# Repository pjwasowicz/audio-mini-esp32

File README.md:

# Audio mini: a small stereo amplifier with Spotify, on an ESP32

*Polska wersja niżej: [przejdź do opisu po polsku](#audio-mini-mały-wzmacniacz-stereo-ze-spotify-na-esp32).*

*Audio mini with the lid off: the class-D amplifier module on the left, the 24 V power supply on the
right, the controller board with the ESP32 at the back, and the 14-segment display and volume knob on
the front panel.*

What I wanted was simple: pick up my phone, choose "Audio mini" in Spotify, and hear music from my
speakers. The TV and the turntable had to keep working too, all from one knob and one remote, with no
extra box that needs its own app.

So I built a small amplifier that does it. Inside the aluminium case there's a class-D amplifier module
(HW-576), a 24 V power supply and the controller board from this repository. The controller plays
Spotify, switches between Spotify, TV and the turntable with relays, and sets the volume with an analog
chip, so the TV and records never go through anything digital. The knob, the remote, the Spotify app
and a small web page all control the same volume. Turn the knob and the slider on your phone moves
with it.

It started on a Raspberry Pi. That worked, but a Pi is a whole computer to look after: an SD card, an
operating system, updates, and a slow start. The ESP32 version is ready a few seconds after you switch
it on, needs no looking after, and costs a fraction of the price.

## Using it

You pick "Audio mini" in the Spotify app like any other Connect speaker (you need Premium). Anyone at
home can connect from their own phone and account. After a power cut it remembers the last login and
connects again by itself.

Press play in Spotify and the amplifier switches to Spotify on its own. Switch to TV and Spotify pauses.

The knob, the remote, the phone and the web page all move the same volume. At low volume each click of
the knob is a small 1 dB step, so late-evening listening is easy to set. The shape of the volume curve
can be changed on the web page.

You shouldn't hear a pop when you switch it on or change inputs. The speakers have their own relay and
connect a couple of seconds later, once everything has power, the right input is on and the volume chip
has confirmed its settings twice.

On Spotify, after 30 seconds of silence the speakers disconnect and the display dims to a clock. TV and
the turntable switch off after 3 hours if nobody touches anything; press 2 or 3 on the remote to bring
them back.

The display is four red 14-segment characters, like on an 80s tuner. It shows the time, the scrolling
title and artist, "V 42" while you turn the volume, and the input name. On TV and the turntable a small
dot next to the clock tells you which one is on.

The remote is the cheap 21-button infrared kind: volume, play and pause, next and previous track,
inputs 1, 2 and 3, and mute.

The web page (`http://<device-address>:8080`) shows what's playing with the album cover, the volume,
the inputs, the volume curve and a few numbers about the device, like Wi-Fi signal and version.

To change the Wi-Fi network you don't need a computer: choose "CONF" in the knob menu, connect your
phone to the "Audio mini config" network, pick your home network and type the password.

New firmware goes over Wi-Fi with `make ota`, so the case stays closed.

## Setting it up

### The knob menu

Press the knob once and the display starts blinking the current input. Turn the knob to pick
`SPOT`, ` TV `, `PHON` or `CONF`, then press again to confirm. If you leave it alone for 8 seconds,
the menu closes without changing anything.

### Connecting to your Wi-Fi

You only need to do this once, or when you change your router or password.

1. Press the knob, turn to `CONF` and press again. The box restarts, and the display scrolls
   `WIFI: AUDIO MINI CONFIG 192.168.4.1`. Music stops while it's in this mode, but the inputs and the
   volume still work.
2. On your phone, open the Wi-Fi settings and join the network called **Audio mini config**. It has no
   password.
3. A setup page should open by itself, the same way hotel Wi-Fi login pages do. If it doesn't, open a
   browser and go to `192.168.4.1`.
4. Pick your home network from the list. For a hidden network, choose the last item,
   "Inna (ukryta) sieć…", and type its name in the box that appears.
5. Type your Wi-Fi password in the "Hasło" field and press "Zapisz i połącz". The page is in Polish,
   but those are the only two things to fill in.
6. The box restarts and joins your network. Your phone goes back to your home Wi-Fi on its own.

If nothing is saved within 5 minutes, the box gives up and starts normally with the old settings.

When the box can't reach your network, the display scrolls one of these instead of the clock:

| Message | What it means | What to do |
|---|---|---|
| `BAD WIFI PASSWORD` | the router turned the password down | run `CONF` again and retype it |
| `NO NETWORK` | it can't see a network with that name | check the name, or move the box closer to the router |
| `NO WIFI` | something else, often the router restarting | wait a minute; it keeps trying by itself |

### Connecting Spotify

1. Make sure your phone is on the same Wi-Fi as the box.
2. Open Spotify, start any song, tap the speaker icon at the bottom and choose **Audio mini**.
3. That's it. The box remembers the account and reconnects by itself after a power cut. Someone else at
   home can pick Audio mini from their own phone and account at any time.

### Finding the web page

The web page lives at `http://<device-address>:8080`. The easiest way to find the address is your
router's list of connected devices; the box shows up as `audio-mini`. On a Mac or iPhone,
`http://audio-mini.local:8080` usually works too.

### Settings for people building their own

The device name shown in Spotify, the network name, the pins and the `make ota` password are set at
build time in the "Audio mini (ESP32)" section of `idf.py menuconfig`. The defaults match the board in `pcb/`.

## The hardware

| Part | What it does | Connection |
|---|---|---|
| ESP32-DevKitC-VIE (ESP32-WROVER-IE, 8 MB PSRAM, external antenna) | brain, Wi-Fi, Spotify | (none) |
| PCM5102A DAC module | Spotify audio → analog | I2S: BCK 26, LCK 25, DIN 27 |
| PT2258 | analog volume control | I2C 0x44 (SDA 21, SCL 22) |
| HT16K33 + 4 × 14-segment LED (0.54") | display | I2C 0x70 |
| 3 relays | input selection Spotify / TV / Phono | GPIO 19 / 18 / 23 |
| relay | speakers on/off | ZAP1, GPIO 13 |
| VS1838 IR receiver + 21-button NEC remote | remote control | ZAP2, GPIO 5 |
| EC11 rotary encoder with button | volume and menu | A 32, B 33, button 14 |
| spare connector | for future ideas | ZAP3, GPIO 15 |

The KiCad files are in `pcb/`: `input_selector` is the main board (there's a PDF of the schematic too)
and `speaker_delay` is the small speaker relay board. The pictures below are 3D views from KiCad. The
ESP32, the DAC and the power module have no 3D models, so you only see their outlines.

| Main board (`input_selector`) | Speaker relay boards (`speaker_delay`) |
|---|---|
|  |  |

Along the top of the main board are the three input relays, the PT2258 volume chip and two regulators
that make 9 V for the volume chip and 12 V for the relays from the amplifier's 24 V. Along the bottom: the DAC module on the left, the ESP32 in the middle, and on the
right the spot for an LM2596 converter (U4), which I later swapped for a separate 5 V adapter.

### What I learned building it

The ESP32 needs its own 5 V power supply. When it shared power with the audio part, through either a
switching converter or a plain regulator, you could hear Wi-Fi in the speakers as a faint buzz. A
separate 5 V / 2 A adapter made it silent.

The DAC is much louder than the other inputs. The PCM5102A puts out about 2.1 V, several times more
than a TV or a turntable preamp, and Spotify came through far too loud even with the volume chip's
input turned well down. For now the firmware turns Spotify down 10 dB before the DAC and the volume chip
turns that input down another 78 dB. On the next board I'd put two resistors after the DAC to bring it
down to the level of the other inputs.

The relays disturb the wires to the volume chip. A command sent right after a relay clicked sometimes
arrived garbled, and the amplifier suddenly played very loud. Now the firmware sends all volume
settings again, twice, just before the speakers connect.

GPIO 5 is a bad pin for a relay. The ESP32 pulls it high while it starts, so anything on it switches on
before the program runs. The infrared receiver is happy there.

4 MB of flash is tight. With room for two copies of the firmware, needed for updates over Wi-Fi, about
100 KB is left. Next time I'd use the 8 or 16 MB version of the same module.

## Building and flashing

You need [ESP-IDF 5.5](https://docs.espressif.com/projects/esp-idf/) in `~/esp/esp-idf`. The Makefile
does the rest.

```bash
make            # first run asks for your Wi-Fi, downloads cspot and applies the patches
make flash      # flash over USB (PORT=/dev/cu.usbserial-XXXX if needed)
make ota        # flash over Wi-Fi (ADRES=192.168.1.130 by default)
make monitor    # serial log
make wifi       # change the Wi-Fi network stored at build time
```

Your Wi-Fi name and password stay in `sdkconfig.local`, which isn't in the repository. A network set
from the "CONF" menu wins over it. If you want `make ota` to ask for a password, set
`CONFIG_AUDIO_OTA_HASLO` in `menuconfig`; there's none by default.

The version number is `PROJECT_VER` in `CMakeLists.txt`. The display shows it for a few seconds after
switching on, and it's also in `/api/system`.

### Updating over Wi-Fi

Once the first version is on the board (over USB, with `make flash`), every later update can go over
Wi-Fi. The box can stay closed and connected to the amplifier.

```bash
make ota                          # builds and sends the new firmware to 192.168.1.130
make ota ADRES=192.168.1.57       # if your box has a different address
```

While it uploads, the display counts up (`U 12`, `U 45`, …). When it's done the box restarts by itself
and shows the new version number for a few seconds. Your settings stay as they were: Wi-Fi, the
Spotify login, volume and input. The whole thing takes about half a minute.

The flash holds two copies of the firmware. The new one is written next to the running one, and the box
only switches over once the upload is complete and checked, so a dropped connection halfway through
changes nothing. There's no automatic way back, though: if the new version doesn't start properly, you
need the USB cable again.

## Under the hood

The Spotify part isn't mine. It comes from [cspot](https://github.com/feelfreelinux/cspot), an
open-source Spotify client small enough to fit on a chip like the ESP32. The first `make` runs
`setup.sh`, which downloads it and applies my fixes from `patches/`.

Those fixes took most of the time. At first the box would play for a few minutes and then restart on its
own, usually right when I pressed pause or switched to TV. Once I tracked them down, the causes were:

- When you pause, the music fades out over half a second. The fade-out code went one step too far and
  wrote into memory that belonged to something else. That alone explains most of the restarts.
- The audio buffer had its "full" check backwards. When it filled up, bits of sound were cut off and
  the rest slid out of place.
- Every time the connection to Spotify dropped and came back, the part of the program that handles it
  ran out of working memory and crashed.
- The knob, the remote and the web page could all talk to Spotify at the same moment, and the library
  wasn't built for that.
- Right after start, a timer decided Spotify had been silent for ages and hung up.

On a weaker Wi-Fi signal the sound still stuttered. Two changes fixed it: a bigger buffer, now 9 seconds
of music, and switching off a sound-processing step that touched every sample even though it only does
anything during the pause fade-out. The chip was spending a lot of time on it, and decoding barely kept
up.

If you want to poke at it: the web page uses a small JSON API (`/api/status`, `/api/system`,
`/api/wejscie`, `/api/strojenie`, `/api/resety`). `/api/resety` lists the last ten restarts and why they
happened. Without it I would not have found the bugs above.

The full story of each bug, with the code and the fix, is in [docs/cspot-bledy.md](docs/cspot-bledy.md).

Code comments are in Polish.

## License

GPL-3.0 (see `LICENSE`), the same as cspot, which the Spotify part is built on.

---

# Audio mini: mały wzmacniacz stereo ze Spotify, na ESP32

*Audio mini bez pokrywy: moduł wzmacniacza klasy D z lewej, zasilacz 24 V z prawej, płytka sterownika
z ESP32 z tyłu, a na panelu przednim wyświetlacz 14-segmentowy i gałka głośności.*

Chciałem prostej rzeczy: biorę telefon, wybieram w Spotify „Audio mini” i słyszę muzykę z moich
kolumn. Telewizor i gramofon miały działać dalej, wszystko z jednej gałki i jednego pilota, bez
kolejnego pudełka z osobną aplikacją.

Zbudowałem więc mały wzmacniacz, który to robi. W aluminiowej obudowie jest moduł wzmacniacza klasy D
(HW-576), zasilacz 24 V i płytka sterownika z tego repozytorium. Sterownik gra Spotify, przełącza
przekaźnikami między Spotify, telewizorem i gramofonem, a głośność ustawia analogowym układem, więc
dźwięk z telewizora i z płyt nie przechodzi przez nic cyfrowego. Gałka, pilot, aplikacja Spotify i mała
strona WWW sterują tą samą głośnością. Kręcisz gałką, a suwak w telefonie przesuwa się razem z nią.

Zaczęło się od Raspberry Pi. Działało, ale Pi to cały komputer do pilnowania: karta SD, system,
aktualizacje i długi start. Wersja na ESP32 jest gotowa kilka sekund po włączeniu, nie trzeba się nią
opiekować i kosztuje ułamek ceny.

## Jak się z tego korzysta

„Audio mini” wybierasz w aplikacji Spotify jak każdy inny głośnik Connect (potrzebne jest Premium).
Każdy domownik może się połączyć ze swojego telefonu i konta. Po zaniku prądu urządzenie pamięta
ostatnie logowanie i łączy się samo.

Wciskasz „play” w Spotify i wzmacniacz sam przełącza się na Spotify. Przełączasz na telewizor
i Spotify się pauzuje.

Gałka, pilot, telefon i strona WWW przesuwają tę samą głośność. Przy cichym graniu każdy ząbek gałki to
mały krok o 1 dB, więc wieczorem łatwo trafić w odpowiedni poziom. Kształt krzywej głośności można
zmienić na stronie WWW.

Przy włączaniu i zmianie wejścia nie powinno nic stuknąć. Kolumny mają własny przekaźnik i dołączają
się kilka sekund później, gdy wszystko ma już zasilanie, włączone jest właściwe wejście, a układ
głośności dwa razy potwierdził ustawienia.

Na Spotify po 30 sekundach ciszy kolumny się odłączają, a wyświetlacz przygasa do zegara. Telewizor
i gramofon wyłączają się po 3 godzinach, jeśli nikt niczego nie dotyka; przycisk 2 albo 3 na pilocie
włącza je z powrotem.

Wyświetlacz to cztery czerwone znaki 14-segmentowe, jak w tunerze z lat 80. Pokazuje godzinę,
przewijany tytuł i wykonawcę, „V 42” przy kręceniu głośnością i nazwę wejścia. Na telewizorze
i gramofonie mała kropka przy zegarze mówi, które z nich gra.

Pilot to ten tani, na podczerwień, z 21 przyciskami: głośność, pauza, następny i poprzedni utwór,
wejścia 1, 2 i 3 oraz wyciszenie.

Strona WWW (`http://<adres-urządzenia>:8080`) pokazuje, co gra, razem z okładką, a do tego głośność,
wejścia, krzywą głośności i kilka liczb o urządzeniu, na przykład siłę Wi-Fi i wersję.

Do zmiany sieci Wi-Fi nie potrzeba komputera: w menu gałki wybierasz „CONF”, łączysz telefon z siecią
„Audio mini config”, wybierasz swoją sieć i wpisujesz hasło.

Nowy program idzie przez Wi-Fi poleceniem `make ota`, więc obudowa zostaje zamknięta.

## Pierwsze uruchomienie

### Menu gałki

Wciśnij gałkę raz, a wyświetlacz zacznie migać nazwą obecnego wejścia. Kręć, żeby wybrać `SPOT`,
` TV `, `PHON` albo `CONF`, i wciśnij jeszcze raz, żeby zatwierdzić. Jeśli przez 8 sekund nic nie
ruszysz, menu zamknie się bez zmian.

### Połączenie z Twoim Wi-Fi

Robisz to raz, albo po zmianie routera lub hasła.

1. Wciśnij gałkę, przekręć do `CONF` i wciśnij jeszcze raz. Urządzenie uruchomi się ponownie,
   a wyświetlacz zacznie przewijać `WIFI: AUDIO MINI CONFIG 192.168.4.1`. W tym trybie Spotify nie gra,
   ale wejścia i głośność działają.
2. W telefonie otwórz ustawienia Wi-Fi i połącz się z siecią **Audio mini config**. Nie ma hasła.
3. Strona konfiguracji powinna otworzyć się sama, tak jak strony logowania do Wi-Fi w hotelu. Jeśli się
   nie otworzy, wpisz w przeglądarce `192.168.4.1`.
4. Wybierz swoją sieć z listy. Dla sieci ukrytej wybierz ostatnią pozycję, „Inna (ukryta) sieć…”,
   i wpisz jej nazwę w polu, które się pojawi.
5. Wpisz hasło do Wi-Fi w polu „Hasło” i naciśnij „Zapisz i połącz”.
6. Urządzenie uruchomi się ponownie i połączy z Twoją siecią. Telefon sam wróci do domowego Wi-Fi.

Jeśli przez 5 minut nic nie zapiszesz, urządzenie odpuści i wystartuje normalnie, ze starymi
ustawieniami.

Gdy urządzenie nie może połączyć się z siecią, zamiast zegara przewija jeden z napisów:

| Napis | Co znaczy | Co zrobić |
|---|---|---|
| `BAD WIFI PASSWORD` | router odrzucił hasło | wejdź jeszcze raz w `CONF` i wpisz je ponownie |
| `NO NETWORK` | nie widzi sieci o tej nazwie | sprawdź nazwę albo przestaw urządzenie bliżej routera |
| `NO WIFI` | coś innego, często restart routera | poczekaj chwilę, łączy się samo |

### Połączenie ze Spotify

1. Sprawdź, czy telefon jest w tej samej sieci Wi-Fi co urządzenie.
2. Otwórz Spotify, puść dowolny utwór, dotknij ikony głośnika na dole i wybierz **Audio mini**.
3. To wszystko. Urządzenie zapamięta konto i po zaniku prądu połączy się samo. Inny domownik może
   w każdej chwili wybrać Audio mini ze swojego telefonu i konta.

### Gdzie jest strona WWW

Strona jest pod adresem `http://<adres-urządzenia>:8080`. Najłatwiej znaleźć adres na liście
podłączonych urządzeń w routerze; urządzenie widać tam jako `audio-mini`. Na Macu i iPhonie zwykle
działa też `http://audio-mini.local:8080`.

### Ustawienia dla budujących

Nazwę widoczną w Spotify, nazwę w sieci, piny i hasło do `make ota` ustawia się przed kompilacją
w części „Audio mini (ESP32)” w `idf.py menuconfig`. Domyślne wartości pasują do płytki z `pcb/`.

## Sprzęt

| Element | Do czego | Połączenie |
|---|---|---|
| ESP32-DevKitC-VIE (ESP32-WROVER-IE, 8 MB PSRAM, antena zewnętrzna) | mózg, Wi-Fi, Spotify | (brak) |
| moduł DAC PCM5102A | dźwięk Spotify → analog | I2S: BCK 26, LCK 25, DIN 27 |
| PT2258 | analogowa regulacja głośności | I2C 0x44 (SDA 21, SCL 22) |
| HT16K33 + 4 × LED 14-seg (0,54") | wyświetlacz | I2C 0x70 |
| 3 przekaźniki | wybór wejścia Spotify / TV / Phono | GPIO 19 / 18 / 23 |
| przekaźnik | dołączanie kolumn | ZAP1, GPIO 13 |
| odbiornik IR VS1838 + pilot NEC 21 przycisków | pilot | ZAP2, GPIO 5 |
| enkoder EC11 z przyciskiem | głośność i menu | A 32, B 33, przycisk 14 |
| wolne złącze | na przyszłe pomysły | ZAP3, GPIO 15 |

Pliki KiCad są w `pcb/`: `input_selector` to płyta główna (schemat jest też w PDF), a `speaker_delay`
to mała płytka przekaźnika kolumn. Obrazki niżej to widoki 3D z KiCad. ESP32, DAC i moduł zasilania nie
mają modeli 3D, więc widać tylko ich obrysy.

| Płyta główna (`input_selector`) | Płytki przekaźnika kolumn (`speaker_delay`) |
|---|---|
|  |  |

U góry płyty głównej są trzy przekaźniki wejść, układ głośności PT2258 i dwa stabilizatory, które
z 24 V wzmacniacza robią 9 V dla układu głośności i 12 V dla przekaźników.
Na dole: moduł DAC z lewej, ESP32 w środku, a z prawej miejsce na przetwornicę LM2596 (U4), którą
później zamieniłem na osobny zasilacz 5 V.

### Czego się nauczyłem przy budowie

ESP32 potrzebuje osobnego zasilacza 5 V. Gdy dzielił zasilanie z częścią audio, czy to przez
przetwornicę, czy przez zwykły stabilizator, Wi-Fi było słychać w kolumnach jako ciche brzęczenie.
Osobny zasilacz 5 V / 2 A dał ciszę.

DAC jest dużo głośniejszy od pozostałych wejść. PCM5102A daje około 2,1 V, kilka razy więcej niż
telewizor czy przedwzmacniacz gramofonowy, i Spotify grało o wiele za głośno, nawet przy mocno
ściszonym wejściu w układzie głośności. Na razie program ścisza Spotify o 10 dB przed DAC, a układ
głośności to wejście jeszcze o 78 dB. W następnej płytce dałbym dwa rezystory za DAC, żeby sprowadzić
go do poziomu pozostałych wejść.

Przekaźniki zakłócają przewody do układu głośności. Polecenie wysłane tuż po kliknięciu przekaźnika
dochodziło czasem przekłamane i wzmacniacz nagle grał bardzo głośno. Teraz program wysyła wszystkie
ustawienia głośności jeszcze raz, dwa razy, tuż przed dołączeniem kolumn.

GPIO 5 to zły pin na przekaźnik. ESP32 przy starcie ustawia na nim stan wysoki, więc to, co jest do
niego podłączone, włącza się, zanim ruszy program. Odbiornikowi podczerwieni to nie przeszkadza.

4 MB pamięci flash to mało. Przy miejscu na dwie kopie programu, potrzebnym do aktualizacji przez
Wi-Fi, zostaje około 100 KB. Następnym razem wziąłbym ten sam moduł w wersji z 8 albo 16 MB.

## Kompilacja i wgrywanie

Potrzebny jest [ESP-IDF 5.5](https://docs.espressif.com/projects/esp-idf/) w `~/esp/esp-idf`. Resztą
zajmuje się Makefile.

```bash
make            # za pierwszym razem pyta o Wi-Fi, pobiera cspot i nakłada łatki
make flash      # wgranie przez USB (PORT=/dev/cu.usbserial-XXXX, jeśli trzeba)
make ota        # wgranie przez Wi-Fi (domyślnie ADRES=192.168.1.130)
make monitor    # komunikaty z ESP32
make wifi       # zmiana sieci Wi-Fi zapisanej przy kompilacji
```

Nazwa Twojej sieci i hasło zostają w `sdkconfig.local`, którego nie ma w repozytorium. Sieć ustawiona
z menu „CONF” ma przed nią pierwszeństwo. Jeśli chcesz, żeby `make ota` pytało o hasło, ustaw
`CONFIG_AUDIO_OTA_HASLO` w `menuconfig`; domyślnie hasła nie ma.

Numer wersji to `PROJECT_VER` w `CMakeLists.txt`. Wyświetlacz pokazuje go przez kilka sekund po
włączeniu, jest też w `/api/system`.

### Aktualizacja przez Wi-Fi

Gdy pierwsza wersja jest już na płytce (przez USB, `make flash`), każdą następną można wgrać przez
Wi-Fi. Obudowa zostaje zamknięta, a urządzenie podłączone do wzmacniacza.

```bash
make ota                          # kompiluje i wysyła nowy program do 192.168.1.130
make ota ADRES=192.168.1.57       # jeśli Twoje urządzenie ma inny adres
```

W trakcie wysyłania wyświetlacz odlicza (`U 12`, `U 45`, …). Po wszystkim urządzenie samo się
restartuje i przez kilka sekund pokazuje nowy numer wersji. Ustawienia zostają bez zmian: Wi-Fi, login
Spotify, głośność i wejście. Całość trwa około pół minuty.

Pamięć mieści dwie kopie programu. Nowa zapisuje się obok działającej, a urządzenie przełącza się na nią
dopiero wtedy, gdy przyszła w całości i jest sprawdzona, więc przerwane połączenie w połowie niczego nie
psuje. Nie ma za to automatycznego powrotu: jeśli nowa wersja nie wystartuje poprawnie, potrzebny jest
znowu kabel USB.

## Pod spodem

Część od Spotify nie jest moja. To [cspot](https://github.com/feelfreelinux/cspot), otwarty klient
Spotify na tyle mały, że mieści się w ESP32. Przy pierwszym `make` skrypt `setup.sh` pobiera go
i nakłada moje poprawki z `patches/`.

Na te poprawki poszło najwięcej czasu. Na początku urządzenie grało kilka minut i samo się restartowało,
najczęściej wtedy, gdy wciskałem pauzę albo przełączałem na telewizor. Przyczyny okazały się takie:

- Przy pauzie muzyka cichnie przez pół sekundy. Kod tego wyciszania robił o jeden krok za dużo
  i zapisywał w pamięci, która należała do czegoś innego. To tłumaczy większość restartów.
- Bufor dźwięku miał odwrotnie sprawdzane, czy jest pełny. Gdy się zapełnił, kawałki muzyki były
  ucinane, a reszta się rozjeżdżała.
- Za każdym razem, gdy połączenie ze Spotify zrywało się i wracało, części programu, która się tym
  zajmuje, brakowało pamięci roboczej i padała.
- Gałka, pilot i strona WWW mogły odezwać się do Spotify w tej samej chwili, a biblioteka nie była na
  to przygotowana.
- Zaraz po starcie licznik uznawał, że Spotify od dawna milczy, i rozłączał.

Przy słabszym Wi-Fi dźwięk dalej się zacinał. Pomogły dwie zmiany: większy bufor, teraz na 9 sekund
muzyki, i wyłączenie przetwarzania dźwięku, które obrabiało każdą próbkę, choć do czegokolwiek jest
potrzebne tylko przy wyciszaniu na pauzę. Procesor tracił na nie sporo czasu i dekodowanie ledwo
nadążało.

Jeśli chcesz pogrzebać: strona WWW korzysta z małego API w JSON (`/api/status`, `/api/system`,
`/api/wejscie`, `/api/strojenie`, `/api/resety`). `/api/resety` pokazuje dziesięć ostatnich restartów
z przyczyną. Bez niego tych błędów bym nie znalazł.

Dokładny opis każdego błędu, z kodem i poprawką, jest w [docs/cspot-bledy.md](docs/cspot-bledy.md).

Komentarze w kodzie są po polsku.

## Licencja

GPL-3.0 (plik `LICENSE`), tak samo jak cspot, na którym opiera się część od Spotify.

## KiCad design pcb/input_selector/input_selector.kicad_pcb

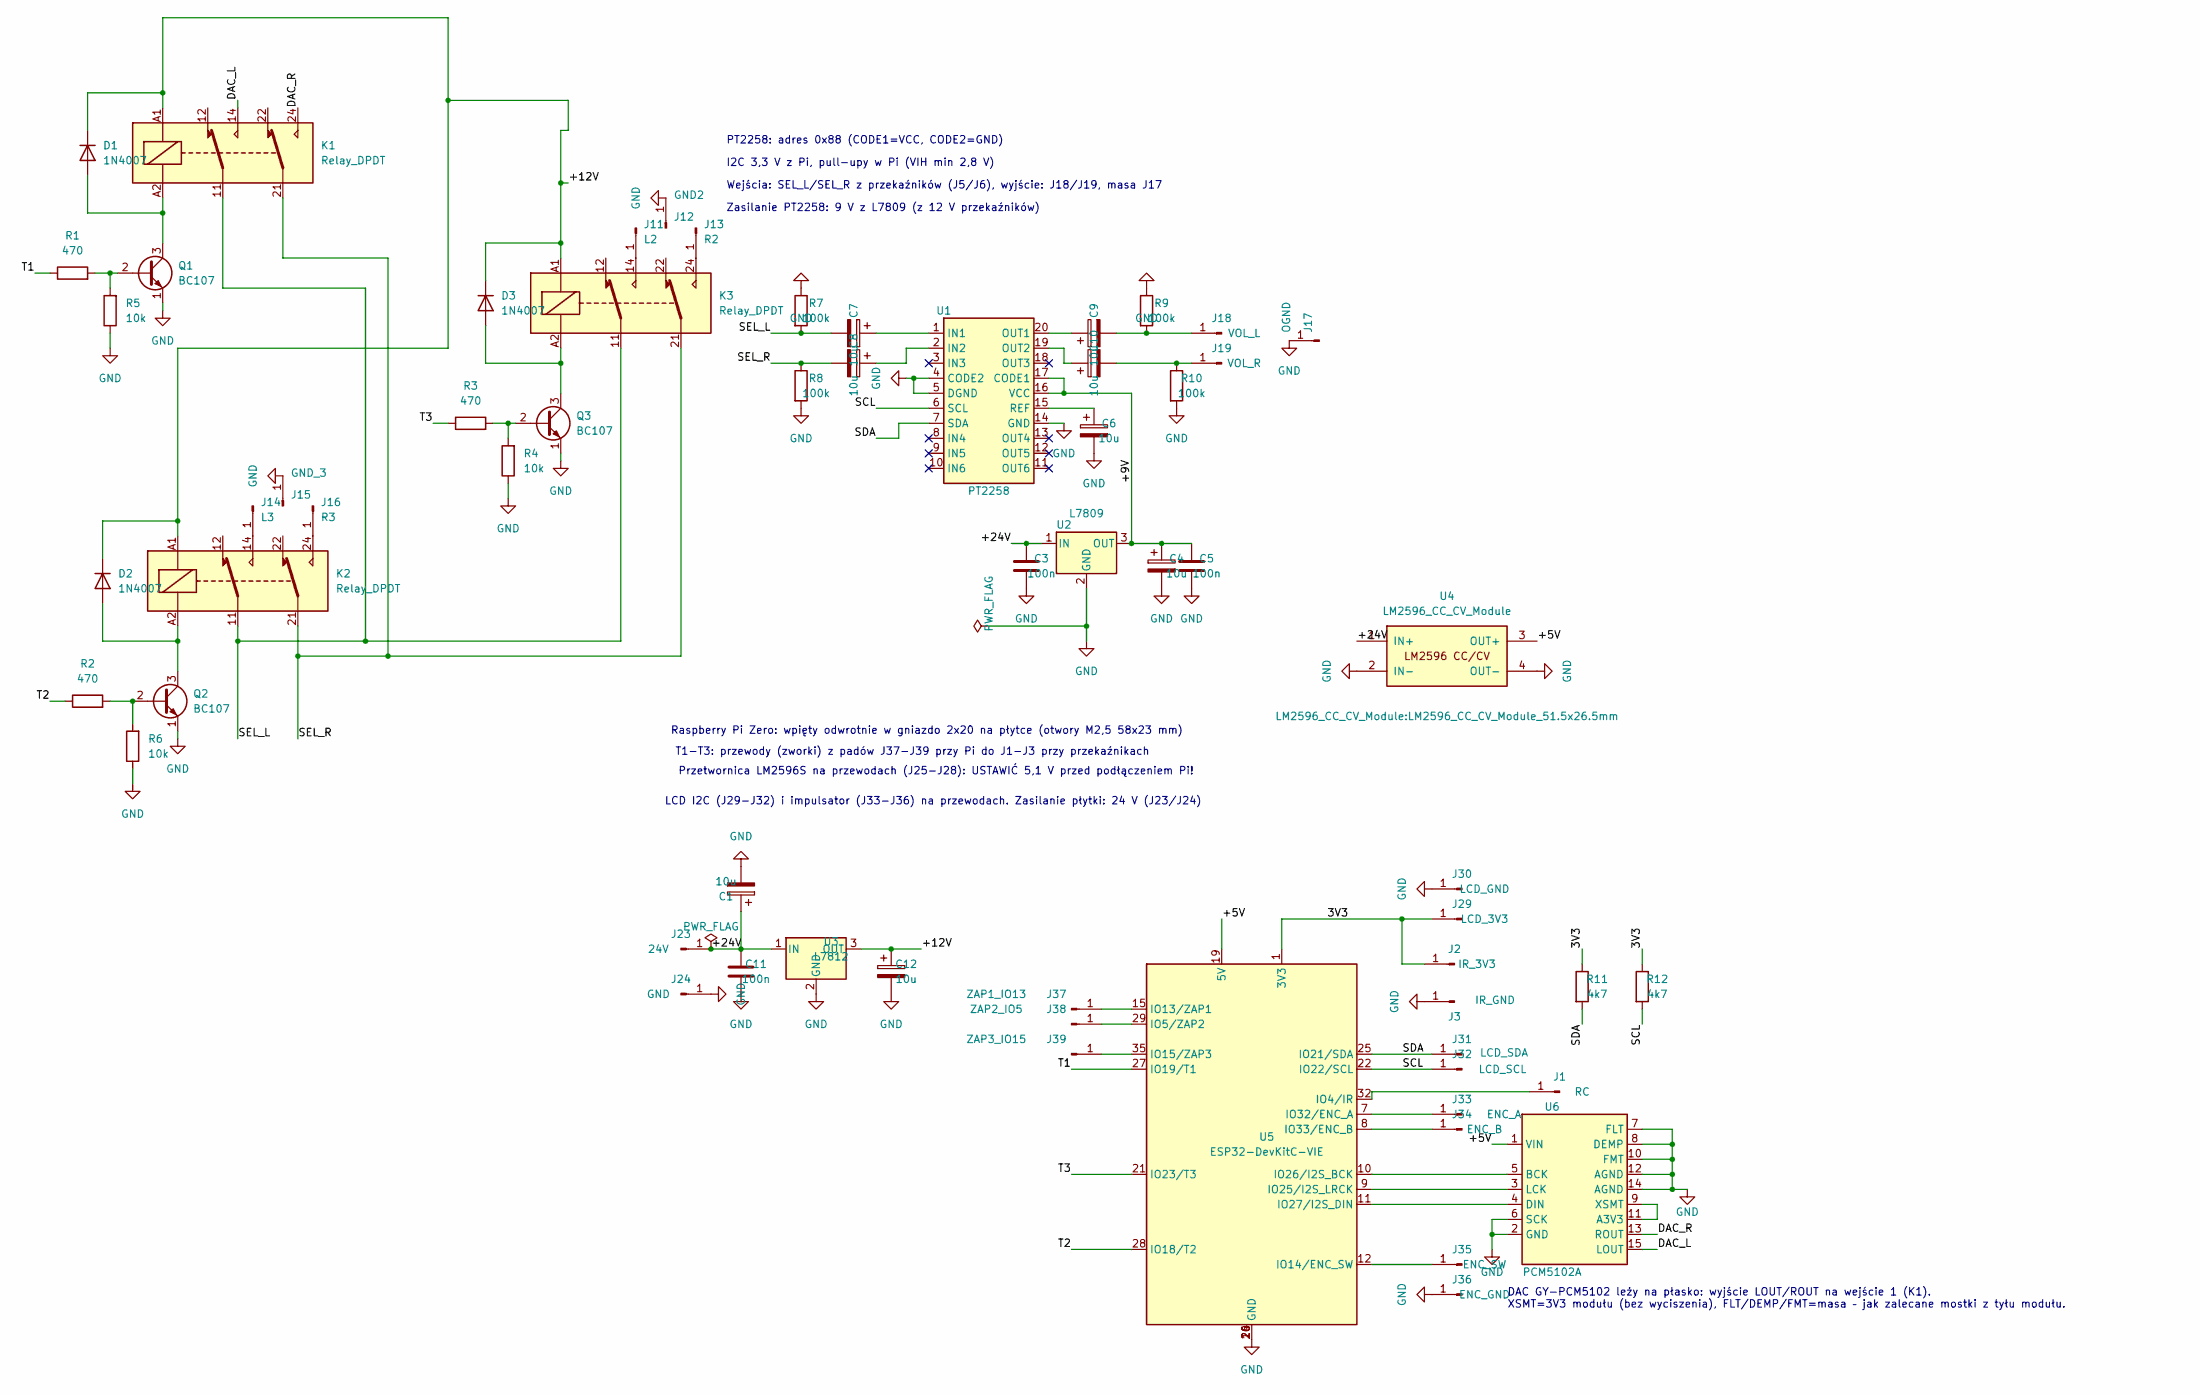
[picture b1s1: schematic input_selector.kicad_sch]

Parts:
C1, C4, C6, C7, C8, C9, C10, C12: 10u; Capacitor_Elyt_d5mm_P2.5mm_Pad2.5x2mm_Hole1mm
C3, C5, C11: 100n; Capacitor_Ceramic_P5mm_W3mm_Pad2.5mm_Hole1mm
D1, D2, D3: 1N4007; Diode_DO35_DO41_P7.62mm_Pad2.5mm_Hole1mm
J1: RC; SolderWire-0.5sqmm_1x01_D0.9mm_OD2.3mm
J2: IR_3V3; SolderWire-0.5sqmm_1x01_D0.9mm_OD2.3mm
J3: IR_GND; SolderWire-0.5sqmm_1x01_D0.9mm_OD2.3mm
J11: L2; SolderWire-0.5sqmm_1x01_D0.9mm_OD2.3mm
J12: GND2; SolderWire-0.5sqmm_1x01_D0.9mm_OD2.3mm
J13: R2; SolderWire-0.5sqmm_1x01_D0.9mm_OD2.3mm
J14: L3; SolderWire-0.5sqmm_1x01_D0.9mm_OD2.3mm
J15: GND_3; SolderWire-0.5sqmm_1x01_D0.9mm_OD2.3mm
J16: R3; SolderWire-0.5sqmm_1x01_D0.9mm_OD2.3mm
J17: OGND; SolderWire-0.5sqmm_1x01_D0.9mm_OD2.3mm
J18: VOL_L; SolderWire-0.5sqmm_1x01_D0.9mm_OD2.3mm
J19: VOL_R; SolderWire-0.5sqmm_1x01_D0.9mm_OD2.3mm
J23: 24V; SolderWire-0.5sqmm_1x01_D0.9mm_OD2.3mm
J24: GND; SolderWire-0.5sqmm_1x01_D0.9mm_OD2.3mm
J29: LCD_3V3; SolderWire-0.5sqmm_1x01_D0.9mm_OD2.3mm
J30: LCD_GND; SolderWire-0.5sqmm_1x01_D0.9mm_OD2.3mm
J31: LCD_SDA; SolderWire-0.5sqmm_1x01_D0.9mm_OD2.3mm
J32: LCD_SCL; SolderWire-0.5sqmm_1x01_D0.9mm_OD2.3mm
J33: ENC_A; SolderWire-0.5sqmm_1x01_D0.9mm_OD2.3mm
J34: ENC_B; SolderWire-0.5sqmm_1x01_D0.9mm_OD2.3mm
J35: ENC_SW; SolderWire-0.5sqmm_1x01_D0.9mm_OD2.3mm
J36: ENC_GND; SolderWire-0.5sqmm_1x01_D0.9mm_OD2.3mm
J37: ZAP1_IO13; SolderWire-0.5sqmm_1x01_D0.9mm_OD2.3mm
J38: ZAP2_IO5; SolderWire-0.5sqmm_1x01_D0.9mm_OD2.3mm
J39: ZAP3_IO15; SolderWire-0.5sqmm_1x01_D0.9mm_OD2.3mm
K1, K2, K3: Relay_DPDT; Relay_DPDT_BIG_PADS
Q1, Q2, Q3: BC107; Transistor_Chip_TO92_P2.54mm_Ammo_Pad2x3mm_Hole1mm
R1, R2, R3: 470; Resistor_0207_P10.16mm_Pad2.5mm_Hole1mm
R4, R5, R6: 10k; Resistor_0207_P10.16mm_Pad2.5mm_Hole1mm
R7, R8, R9, R10: 100k; Resistor_0207_P7.62mm_Pad2.5mm_Hole1mm
R11, R12: 4k7; Resistor_0207_P10.16mm_Pad2.5mm_Hole1mm
U1: PT2258; DIP-20_BIG
U2: L7809; TO-220-3_Vertical
U3: L7812; TO-220-3_Vertical
U4: LM2596_CC_CV_Module; LM2596_CC_CV_Module_51.5x26.5mm
U5: ESP32-DevKitC-VIE; ESP32-DevKitC_2x19_P2.54_Rows25.4
U6: PCM5102A; PCM5102A_Module_GY-PCM5102_Flat

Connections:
/3V3: J2.1, J29.1, R11.1, R12.1, U5.1 (3V3)
/+5V: U4.3 (OUT+), U5.19 (5V), U6.1 (VIN)
/+9V: C4.1, C5.1, U1.16 (VCC), U1.17 (CODE1), U2.3 (OUT)
/+12V: C12.1, D1.1 (K), D2.1 (K), D3.1 (K), K1.A1, K2.A1, K3.A1, U3.3 (OUT)
/+24V: C1.1, C3.1, C11.1, J23.1, U2.1 (IN), U3.1 (IN), U4.1 (IN+)
/DAC_L: K1.14, U6.15 (LOUT)
/DAC_R: K1.24, U6.13 (ROUT)
/SCL: J32.1, R12.2, U1.6 (SCL), U5.22 (IO22/SCL)
/SDA: J31.1, R11.2, U1.7 (SDA), U5.25 (IO21/SDA)
/SEL_L: C7.2, K1.11, K2.11, K3.11, R7.2
/SEL_R: C8.2, K1.21, K2.21, K3.21, R8.1
/T1: R1.1, U5.27 (IO19/T1)
/T2: R2.1, U5.28 (IO18/T2)
/T3: R3.1, U5.21 (IO23/T3)
GND: C1.2, C3.2, C4.2, C5.2, C6.2, C11.2, C12.2, J3.1, J12.1, J15.1, J17.1, J24.1, J30.1, J36.1, Q1.1 (E), Q2.1 (E), Q3.1 (E), R4.1, R5.1, R6.1, R7.1, R8.2, R9.1, R10.2, U1.4 (CODE2), U1.5 (DGND), U1.14 (GND), U2.2 (GND), U3.2 (GND), U4.2 (IN-), U4.4 (OUT-), U5.14 (GND), U5.20 (GND), U5.26 (GND), U6.2 (GND), U6.6 (SCK), U6.7 (FLT), U6.8 (DEMP), U6.10 (FMT), U6.12 (AGND), U6.14 (AGND)
unnamed: D1.2 (A), K1.A2, Q1.3 (C)
unnamed: D2.2 (A), K2.A2, Q2.3 (C)
unnamed: D3.2 (A), K3.A2, Q3.3 (C)
unnamed: J1.1, U5.32 (IO4/IR)
unnamed: J11.1, K3.14
unnamed: J13.1, K3.24
unnamed: J14.1, K2.14
unnamed: J16.1, K2.24
unnamed: C9.2, J18.1, R9.2
unnamed: C10.2, J19.1, R10.1
unnamed: J33.1, U5.7 (IO32/ENC_A)
unnamed: J34.1, U5.8 (IO33/ENC_B)
unnamed: J35.1, U5.12 (IO14/ENC_SW)
unnamed: J37.1, U5.15 (IO13/ZAP1)
unnamed: J38.1, U5.29 (IO5/ZAP2)
unnamed: J39.1, U5.35 (IO15/ZAP3)
unnamed: Q1.2 (B), R1.2, R5.2
unnamed: Q2.2 (B), R2.2, R6.2
unnamed: Q3.2 (B), R3.2, R4.2
unnamed: C7.1, U1.1 (IN1)
unnamed: C8.1, U1.2 (IN2)
unnamed: C9.1, U1.20 (OUT1)
unnamed: C10.1, U1.19 (OUT2)
unnamed: C6.1, U1.15 (REF)
unnamed: U5.9 (IO25/I2S_LRCK), U6.3 (LCK)
unnamed: U5.10 (IO26/I2S_BCK), U6.5 (BCK)
unnamed: U5.11 (IO27/I2S_DIN), U6.4 (DIN)
unnamed: U6.9 (XSMT), U6.11 (A3V3)

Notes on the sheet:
Zasilanie PT2258: 9 V z L7809 (z 12 V przekaźników)
Przetwornica LM2596S na przewodach (J25-J28): USTAWIĆ 5,1 V przed podłączeniem Pi!
I2C 3,3 V z Pi, pull-upy w Pi (VIH min 2,8 V)
PT2258: adres 0x88 (CODE1=VCC, CODE2=GND)
Wejścia: SEL_L/SEL_R z przekaźników (J5/J6), wyjście: J18/J19, masa J17
T1-T3: przewody (zworki) z padów J37-J39 przy Pi do J1-J3 przy przekaźnikach
LCD I2C (J29-J32) i impulsator (J33-J36) na przewodach. Zasilanie płytki: 24 V (J23/J24)
DAC GY-PCM5102 leży na płasko: wyjście LOUT/ROUT na wejście 1 (K1). XSMT=3V3 modułu (bez wyciszenia), FLT/DEMP/FMT=masa – jak zalecane mostki z tyłu modułu.
Raspberry Pi Zero: wpięty odwrotnie w gniazdo 2x20 na płytce (otwory M2,5 58x23 mm)

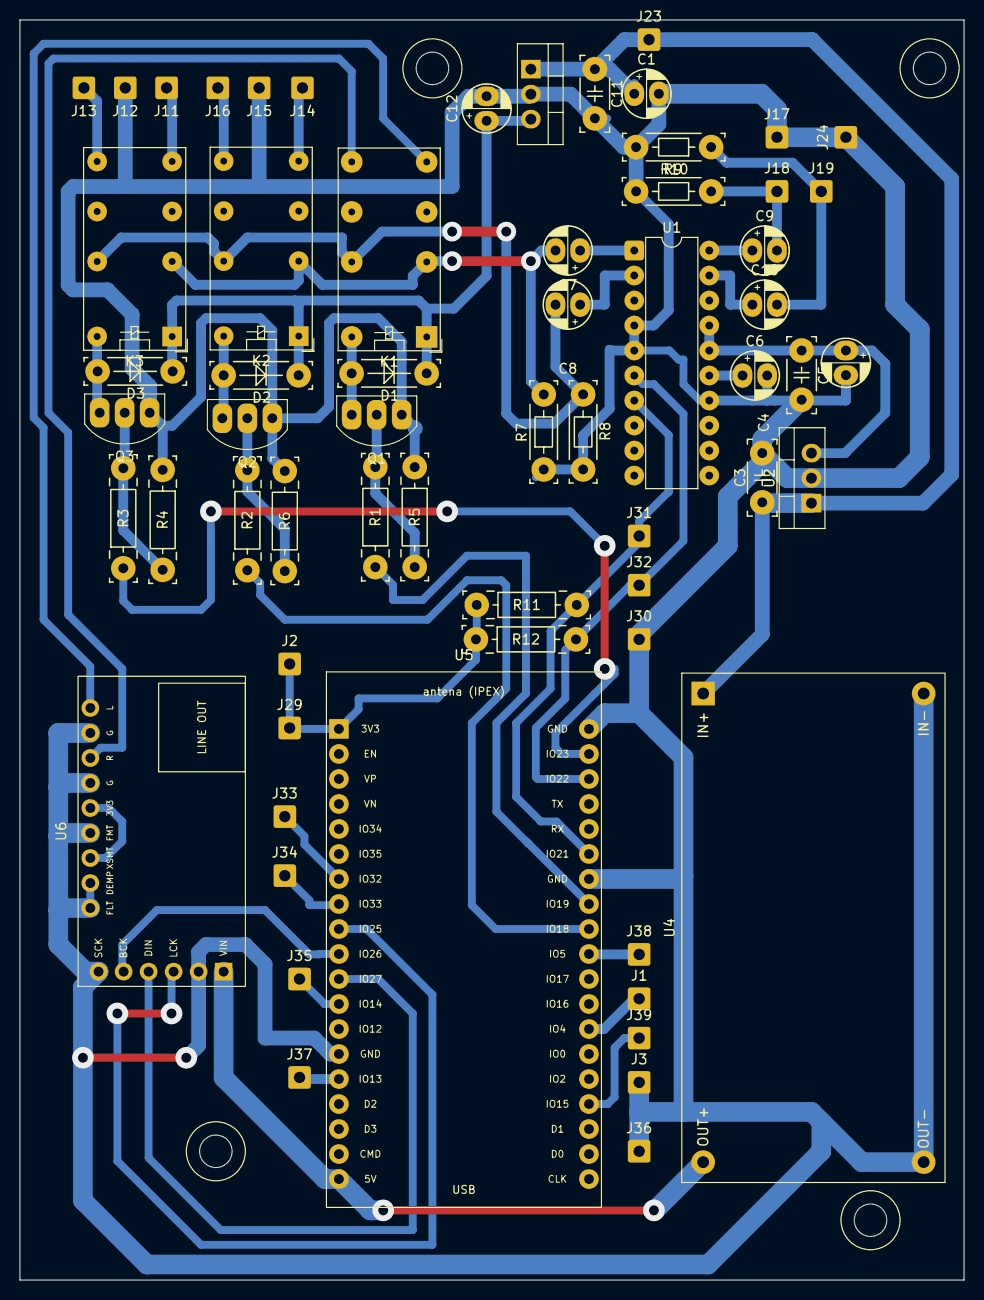
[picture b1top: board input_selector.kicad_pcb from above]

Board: 2 copper layers, 95.9 x 128.0 mm, 67 parts (0 on the bottom side), 43 nets.

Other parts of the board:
H1, H2, H3, H4: M3; MountingHole_3.3mm
